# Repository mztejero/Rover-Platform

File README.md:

# Rover-Platform
ESP-IDF firmware, KiCad PCB, and Fusion360 Cad files  for a Rovere Platform

# ESP-IDF

The file architecture is split into each of the remote's functions with each .c file also havng a complementary .h file allowing variable and function sharng across the project. The files can be found in rover_firmware/main:

```
config.c
encoder.c
imu.c
motor.c
speed_controller.c
uart_interface.c
```

- ```config.c``` Sets up and names the GPIO's used on the ESP32.<br>
- ```encoder.c``` Reads interrupts on quadrature encoders A and B terminals and creates tasks for counting which are added to queues. This file also allows for reading wheel rotation and speed.<br>
- ```imu.c``` Communicates with onboard IMU via I<sup>2</sup>C in order to receive sensor readings from accelerometer and gyroscope.<br>
- ```motor.c``` Generates a PWM signal using timer and compare events and provides a function for controlling motor speed and direction through duty cycle.<br>
- ```speed_controller.c``` Controls motor speed using a PID and non linear gain to adjust duty cycle written to motor. The feedback is obtained from the encoders.<br>
- ```uart_interface.c``` Receives speed commands for all four motors and writes wheel rotation, speed, accelerometer, and gyroscope readings.<br>

  * The files with the extension "_module" were used for the breadboard module prototyping.
  *  There are files for communicating with onboard Magnetometer, however these are not currently being used.

# Schematics

- ESP32-S3-WROOM-1: Microcontroller used to run firmware, read sensors, and write to actuators
- CP2102A USB-to-UART: Interface for UART reading and writing and for uploading code to the ESP32-WROOM-32E. The NPN transistors circuitry automatically put the ESP32 into bootloader mode when a new upload happens.
- TB6612FNG: Dual Motor driver used for interfacing with 2 DC Motors. Uses A and B pins for motor direction and a PWM pin.
- ISM330DHCX: IMU chip used for accelerometer and gyroscope feedback. Uses I<sup>2</sup>C protocol for communication.

Chips not currently used
  • BMM350: Magnetometer chip with I<sup>2</sup>C protocol for communication.

# Final PCB Design

# Final Rover CAD Design

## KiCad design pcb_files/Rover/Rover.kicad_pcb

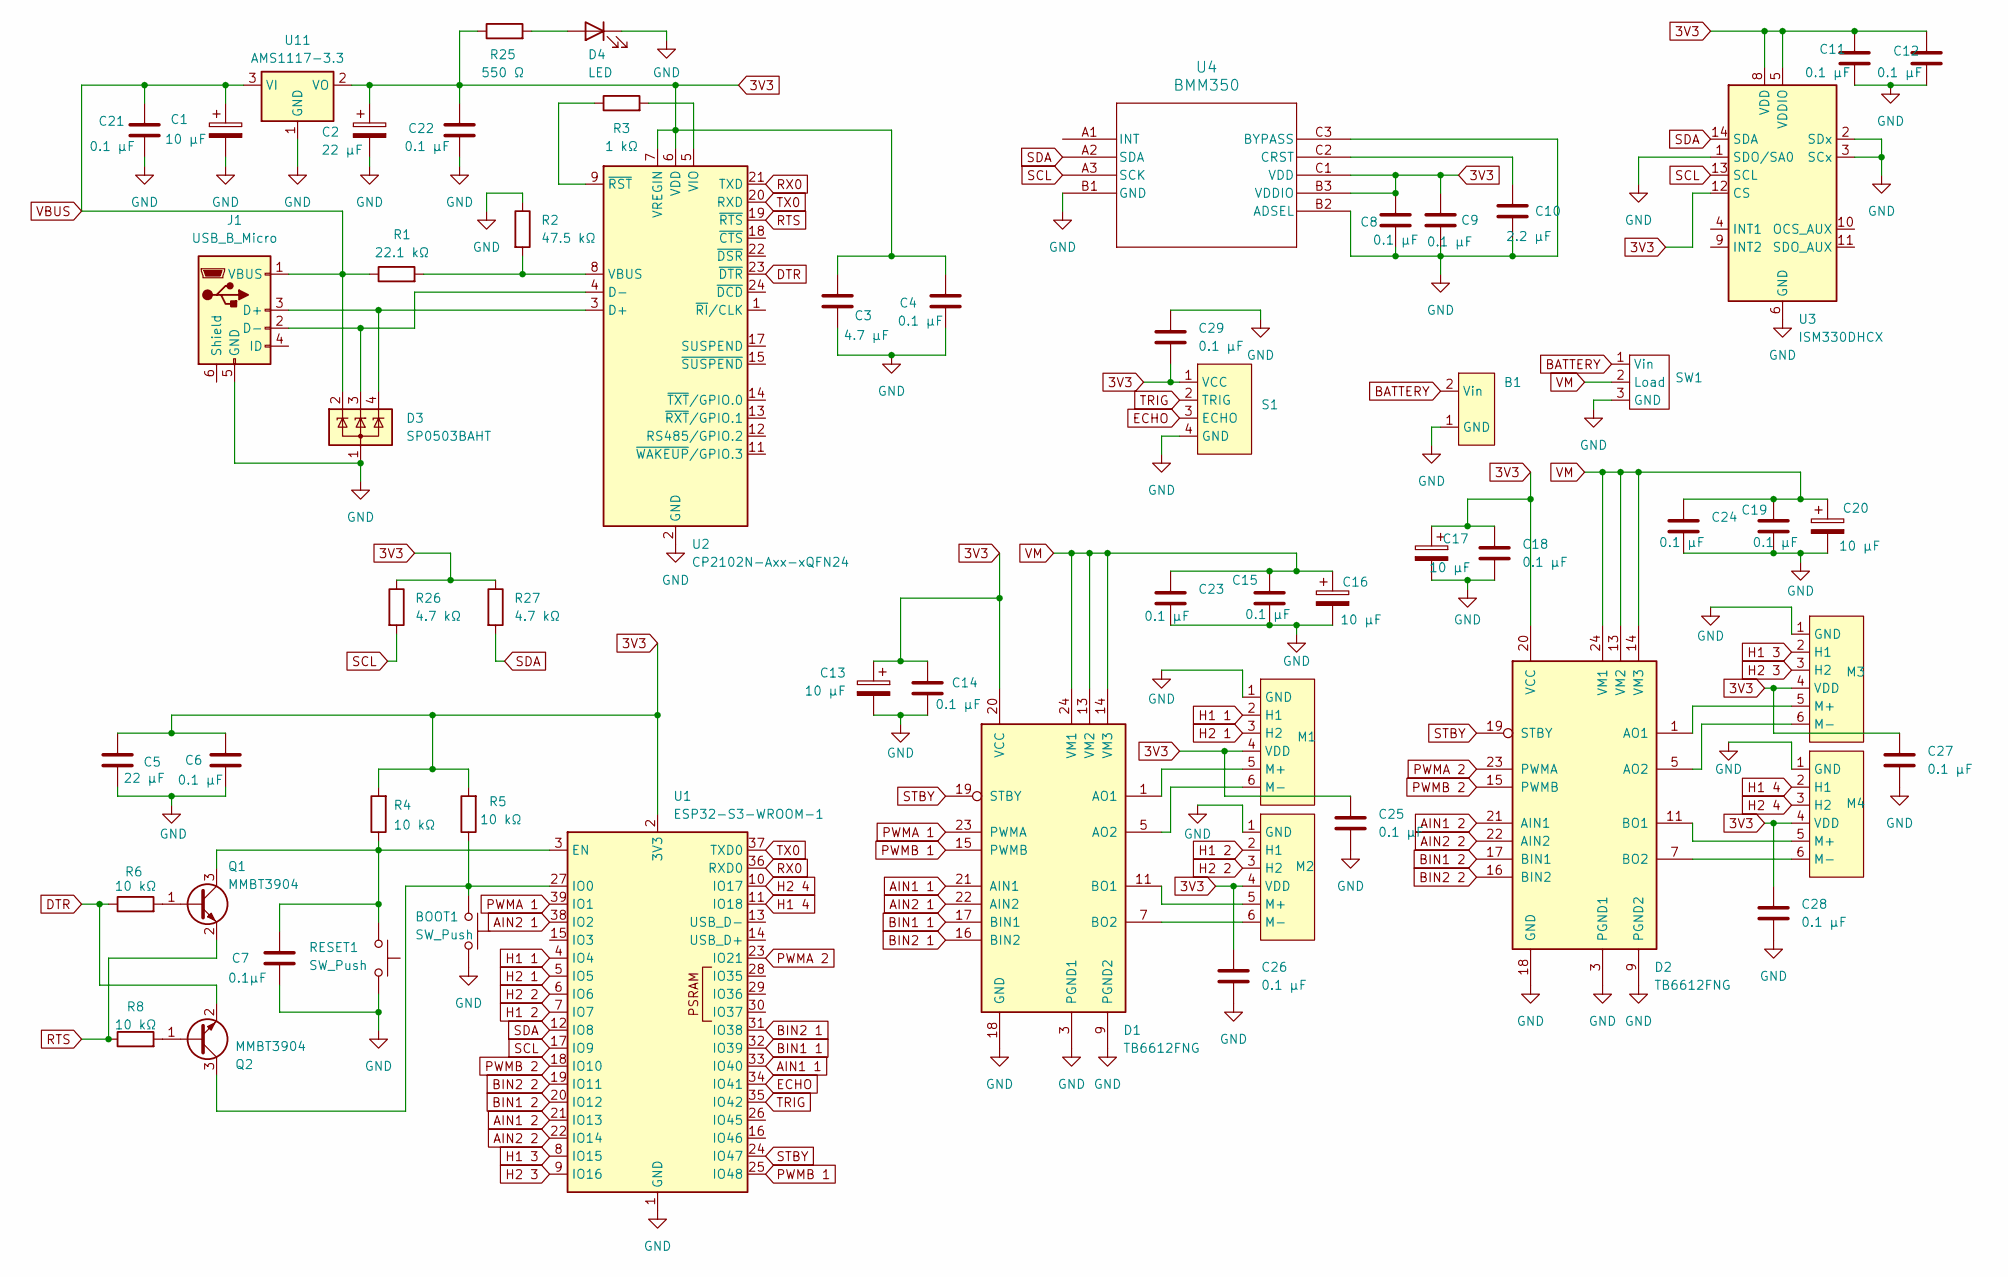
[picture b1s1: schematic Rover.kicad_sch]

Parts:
B1: Battery
BOOT1: SW_Push; SW_SPST_PTS647_Sx38
C1, C13, C16, C17, C20: 10 µF; CP_EIA-2012-12_Kemet-R
C2: 22 µF; CP_EIA-2012-12_Kemet-R
C3: 4.7 µF; C_0805_2012Metric
C4, C6, C8, C9, C11, C12, C14, C15, C18, C19, C21, C22, C23, C24, C25, C26, C27, C28, C29: 0.1 µF; C_0603_1608Metric
C5: 22 µF; C_0805_2012Metric
C7: 0.1µF; C_0603_1608Metric
C10: 2.2 µF; C_0805_2012Metric
D1, D2: TB6612FNG; SSOP-24_5.3x8.2mm_P0.65mm
D3: SP0503BAHT; SOT-143
D4: LED; LED_0603_1608Metric
J1: USB_B_Micro; USB_Micro-B_Amphenol_10103594-0001LF_Horizontal
M1, M2, M3, M4: JST_PH_B6B-PH-K_1x06_P2.00mm_Vertical
Q1, Q2: MMBT3904; SOT-23
R1: 22.1 kΩ; R_0603_1608Metric
R2: 47.5 kΩ; R_0603_1608Metric
R3: 1 kΩ; R_0603_1608Metric
R4, R5, R6, R8: 10 kΩ; R_0603_1608Metric
R25: 550 Ω; R_0603_1608Metric
R26, R27: 4.7 kΩ; R_0603_1608Metric
RESET1: SW_Push; SW_SPST_PTS647_Sx38
S1: JST_PH_B4B-PH-K_1x04_P2.00mm_Vertical
SW1: Switch
U1: ESP32-S3-WROOM-1
U2: CP2102N-Axx-xQFN24; QFN-24-1EP_4x4mm_P0.5mm_EP2.6x2.6mm
U3: ISM330DHCX; LGA-14_3x2.5mm_P0.5mm_LayoutBorder3x4y
U4: BMM350; BGA9_BMM350_BOS
U11: AMS1117-3.3; SOT-223-3_TabPin2

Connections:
3V3: C2.1, C3.1, C4.1, C5.1, C6.1, C8.2, C9.1, C11.1, C12.1, C13.1, C14.1, C17.1, C18.1, C22.1, C25.1, C26.1, C27.1, C28.1, C29.2, D1.20 (VCC), D2.20 (VCC), M1.4 (VDD), M2.4 (VDD), M3.4 (VDD), M4.4 (VDD), R4.2, R5.2, R25.1, R26.1, R27.1, S1.1 (VCC), U1.2 (3V3), U2.6 (VDD), U2.7 (VREGIN), U3.5 (VDDIO), U3.8 (VDD), U3.12 (CS), U4.B3 (VDDIO), U4.C1 (VDD), U11.2 (VO)
AIN1 1: D1.21 (AIN1), U1.33 (IO40)
AIN1 2: D2.21 (AIN1), U1.21 (IO13)
AIN2 1: D1.22 (AIN2), U1.38 (IO2)
AIN2 2: D2.22 (AIN2), U1.22 (IO14)
BATTERY: B1.2 (Vin), SW1.1 (Vin)
BIN1 1: D1.17 (BIN1), U1.32 (IO39)
BIN1 2: D2.17 (BIN1), U1.20 (IO12)
BIN2 1: D1.16 (BIN2), U1.31 (IO38)
BIN2 2: D2.16 (BIN2), U1.19 (IO11)
DTR: Q2.2 (E), R6.1, U2.23 (~DTR)
ECHO: S1.3 (ECHO), U1.34 (IO41)
GND: B1.1 (GND), BOOT1.2, C1.2, C2.2, C3.2, C4.2, C5.2, C6.2, C7.2, C8.1, C9.2, C10.1, C11.2, C12.2, C13.2, C14.2, C15.2, C16.2, C17.2, C18.2, C19.2, C20.2, C21.2, C22.2, C23.2, C24.2, C25.2, C26.2, C27.2, C28.2, C29.1, D1.3 (PGND1), D1.4 (PGND1), D1.9 (PGND2), D1.10 (PGND2), D1.18 (GND), D2.3 (PGND1), D2.4 (PGND1), D2.9 (PGND2), D2.10 (PGND2), D2.18 (GND), D3.1 (A), D4.1 (K), J1.5 (GND), M1.1 (GND), M2.1 (GND), M3.1 (GND), M4.1 (GND), R2.1, RESET1.2, S1.4 (GND), SW1.3 (GND), U1.1 (GND), U1.40 (GND), U1.41 (GND), U2.2 (GND), U2.25 (GND), U3.1 (SDO/SA0), U3.2 (SDx), U3.3 (SCx), U3.6 (GND), U3.7 (GND), U4.B1 (GND), U4.B2 (ADSEL), U4.C3 (BYPASS), U11.1 (GND)
H1 1: M1.2 (H1), U1.4 (IO4)
H1 2: M2.2 (H1), U1.7 (IO7)
H1 3: M3.2 (H1), U1.8 (IO15)
H1 4: M4.2 (H1), U1.11 (IO18)
H2 1: M1.3 (H2), U1.5 (IO5)
H2 2: M2.3 (H2), U1.6 (IO6)
H2 3: M3.3 (H2), U1.9 (IO16)
H2 4: M4.3 (H2), U1.10 (IO17)
unnamed: D4.2 (A), R25.2
unnamed: D3.4 (K), J1.3 (D+), U2.3 (D+)
unnamed: D3.3 (K), J1.2 (D-), U2.4 (D-)
unnamed: D1.1 (AO1), D1.2 (AO1), M1.5 (M+)
unnamed: D1.5 (AO2), D1.6 (AO2), M1.6 (M-)
unnamed: D1.11 (BO1), D1.12 (BO1), M2.5 (M+)
unnamed: D1.7 (BO2), D1.8 (BO2), M2.6 (M-)
unnamed: D2.1 (AO1), D2.2 (AO1), M3.5 (M+)
unnamed: D2.5 (AO2), D2.6 (AO2), M3.6 (M-)
unnamed: D2.11 (BO1), D2.12 (BO1), M4.5 (M+)
unnamed: D2.7 (BO2), D2.8 (BO2), M4.6 (M-)
unnamed: Q1.1 (B), R6.2
unnamed: C7.1, Q1.3 (C), R4.1, RESET1.1, U1.3 (EN)
unnamed: Q2.1 (B), R8.2
unnamed: BOOT1.1, Q2.3 (C), R5.1, U1.27 (IO0)
unnamed: R1.2, R2.2, U2.8 (VBUS)
unnamed: R3.2, U2.5 (VIO)
unnamed: R3.1, U2.9 (~RST)
unnamed: C10.2, U4.C2 (CRST)
PWMA 1: D1.23 (PWMA), U1.39 (IO1)
PWMA 2: D2.23 (PWMA), U1.23 (IO21)
PWMB 1: D1.15 (PWMB), U1.25 (IO48)
PWMB 2: D2.15 (PWMB), U1.18 (IO10)
RTS: Q1.2 (E), R8.1, U2.19 (~RTS)
RX0: U1.36 (RXD0), U2.21 (TXD)
SCL: R26.2, U1.17 (IO9), U3.13 (SCL), U4.A3 (SCK)
SDA: R27.2, U1.12 (IO8), U3.14 (SDA), U4.A2 (SDA)
STBY: D1.19 (STBY), D2.19 (STBY), U1.24 (IO47)
TRIG: S1.2 (TRIG), U1.35 (IO42)
TX0: U1.37 (TXD0), U2.20 (RXD)
VBUS: C1.1, C21.1, D3.2 (K), J1.1 (VBUS), R1.1, U11.3 (VI)
VM: C15.1, C16.1, C19.1, C20.1, C23.1, C24.1, D1.13 (VM2), D1.14 (VM3), D1.24 (VM1), D2.13 (VM2), D2.14 (VM3), D2.24 (VM1), SW1.2 (Load)

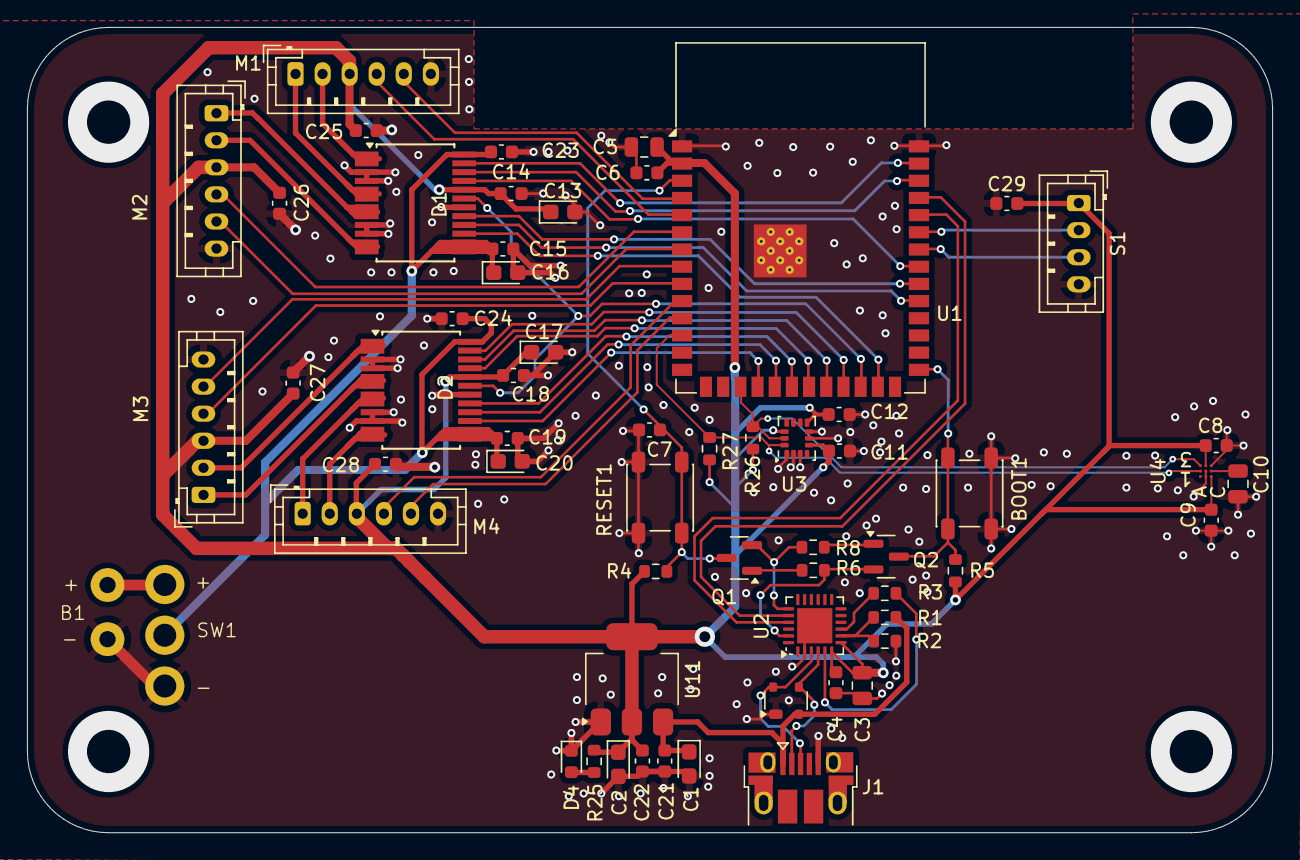
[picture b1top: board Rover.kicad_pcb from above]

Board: 2 copper layers, 92.0 x 59.5 mm, 60 parts (0 on the bottom side), 53 nets.

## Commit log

2026-02-17 updated files
2026-02-17 Rename Rover_side.PNG to Rover_side.png
2026-02-17 Rename ROver_Top.PNG to Rover_Top.png
2026-02-17 Rename PCB.PNG to PCB.png
2026-02-17 update pictures
2026-02-17 png conversion
